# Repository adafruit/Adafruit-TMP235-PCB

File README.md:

## Adafruit TMP235 Plug-and-Play STEMMA Analog Temperature Sensor PCB

<a href="http://www.adafruit.com/products/4686"><br/>
Click here to purchase one from the Adafruit shop</a>

PCB files for the Adafruit TMP235 Plug-and-Play STEMMA Analog Temperature Sensor. 

Format is EagleCAD schematic and board layout
* https://www.adafruit.com/product/4686

### Description

For fans of the TMP36, we now have a very similar analog temperature sensor with a 3-pin JST connector (we call these STEMMA connectors). Unlike many of our temperature sensors, this one is analog output, not I2C, so its best used by a microcontroller with an analog input, as most microcontrollers do.

These sensors are very simple to use, no libraries or complex configurations required. Plug this board into any of our 3-pin JST PH cables (we have ones with header ends, alligator clips, etc) Red goes to 3V to 5V DC power, black wire connects to ground, and white wire connects to an analog input. The voltage out is 0V at -50°C and 1.75V at 125°C. You can easily calculate the temperature from the voltage in millivolts: Temp °C = 100*(reading in V) - 50

### License

Adafruit invests time and resources providing this open source design, please support Adafruit and open-source hardware by purchasing products from [Adafruit](https://www.adafruit.com)!

Designed by Limor Fried/Ladyada for Adafruit Industries.

Creative Commons Attribution/Share-Alike, all text above must be included in any redistribution. 
See license.txt for additional details.

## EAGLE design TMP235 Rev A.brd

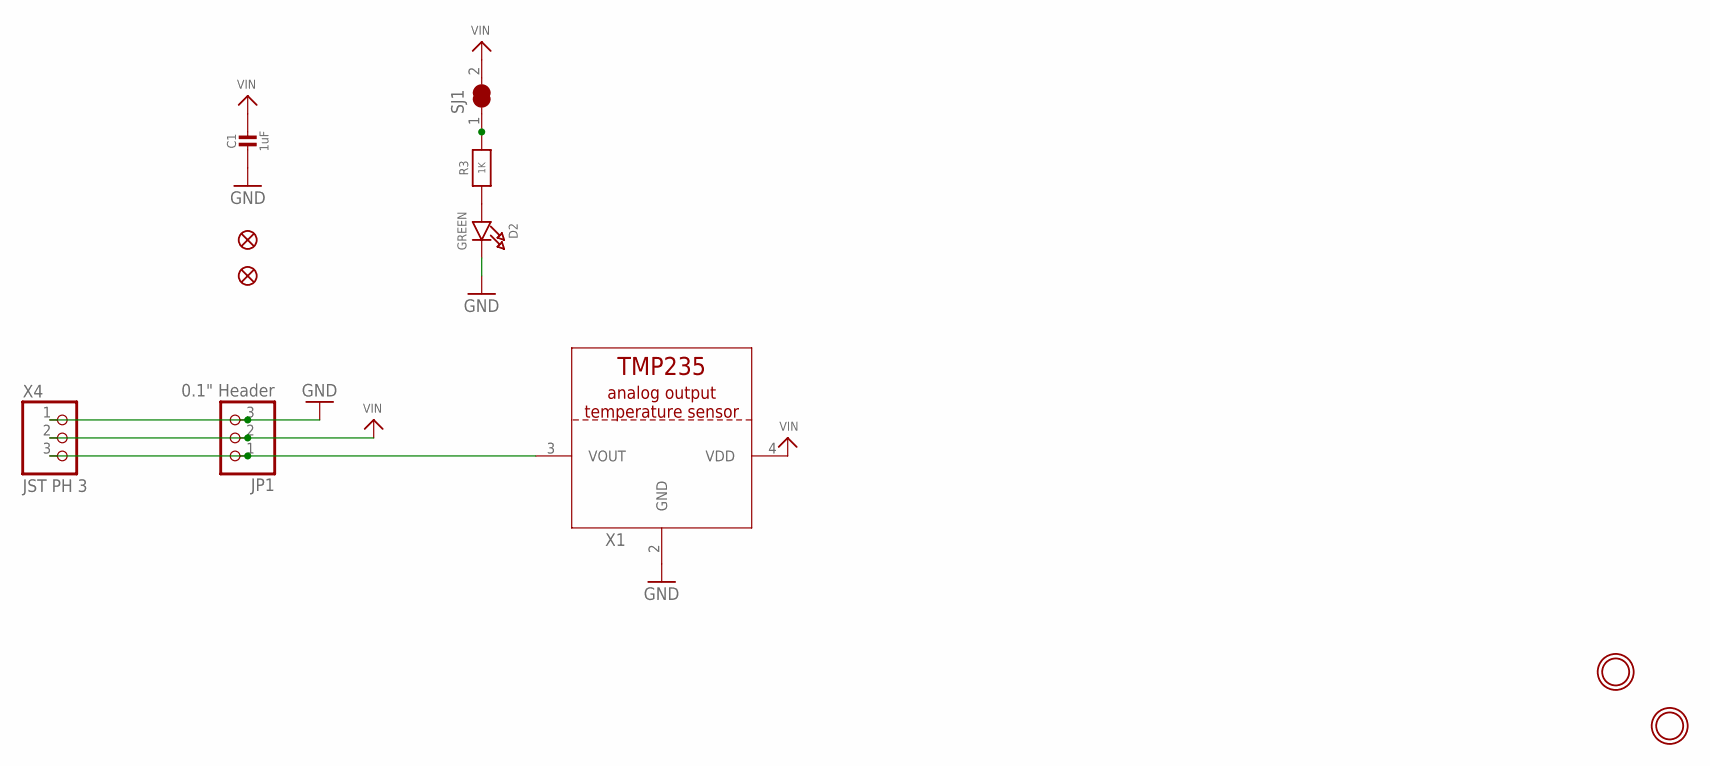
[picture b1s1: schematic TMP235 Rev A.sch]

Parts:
C1: 1uF; 0805-NO
D2: GREEN; CHIPLED_0805_NOOUTLINE
FID2, FID3: FIDUCIAL_1MM
JP1: 0.1" Header; 1X03_OVAL
R3: 1K; 0603-NO
SJ1: SOLDERJUMPER_CLOSED; SOLDERJUMPER_CLOSEDWIRE
U$1, U$8: MOUNTINGHOLE2.5; MOUNTINGHOLE_2.5_PLATED
X1: TMP235_DCKR; SC70-5
X4: JST PH 3; JSTPH3

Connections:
GND: C1.2, D2.C, JP1.3, X1.2 (GND), X4.1
unnamed: R3.2, SJ1.1
unnamed: D2.A, R3.1
SIGNAL: JP1.1, X1.3 (VOUT), X4.3
VIN: C1.1, JP1.2, SJ1.2, X1.4 (VDD), X4.2

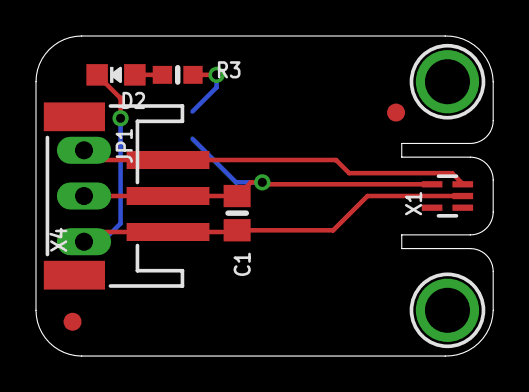
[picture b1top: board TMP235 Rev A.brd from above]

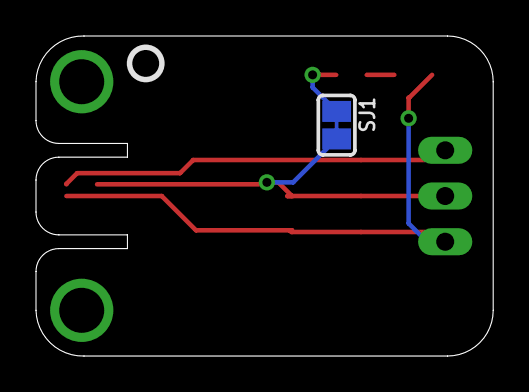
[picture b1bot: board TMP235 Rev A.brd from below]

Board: 2 copper layers, 25.4 x 17.8 mm, 14 parts (3 on the bottom side), 5 nets.

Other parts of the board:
U$5: PCBFEAT-REV-040
U$12: TMP235_BACK
U$13: TMP235_FRONT

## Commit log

2020-09-03 Added board files

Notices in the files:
parts and their libraries:
microbuilder: This work is placed in the public domain, and may be freely used for commercial and non-commercial work with the following conditions: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
